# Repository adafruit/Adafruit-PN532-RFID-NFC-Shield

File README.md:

## Adafruit PN532 RFID/NFC Shield for Arduino
<a href="http://www.adafruit.com/products/789"><br/>
Click here to purchase one from the Adafruit shop</a>

We've taken our popular Adafruit PN532 breakout board and turned it into a shield - the perfect tool for any 13.56MHz RFID or NFC application. The Adafruit NFC shield uses the PN532 chip-set (the most popular NFC chip on the market) and is what is embedded in pretty much every phone or device that does NFC. It can pretty much do it all, such as read and write to tags and cards, communicate with phones (say for payment processing), and 'act' like a NFC tag. If you want to do any sort of embedded NFC work, this is the chip you'll want to use! 

These are the Eagle CAD files for the Adafruit PN532 RFID/NFC Shield for Arduino:
- http://www.adafruit.com/products/789

### License

Adafruit invests time and resources providing this open source design, please support Adafruit and open-source hardware by purchasing products from [Adafruit](https://www.adafruit.com)!

All text above must be included in any redistribution

Designed by Limor Fried/Ladyada and Kevin Townsend for Adafruit Industries.
Creative Commons Attribution/Share-Alike, all text above must be included in any redistribution. 
See license.txt for additional information.

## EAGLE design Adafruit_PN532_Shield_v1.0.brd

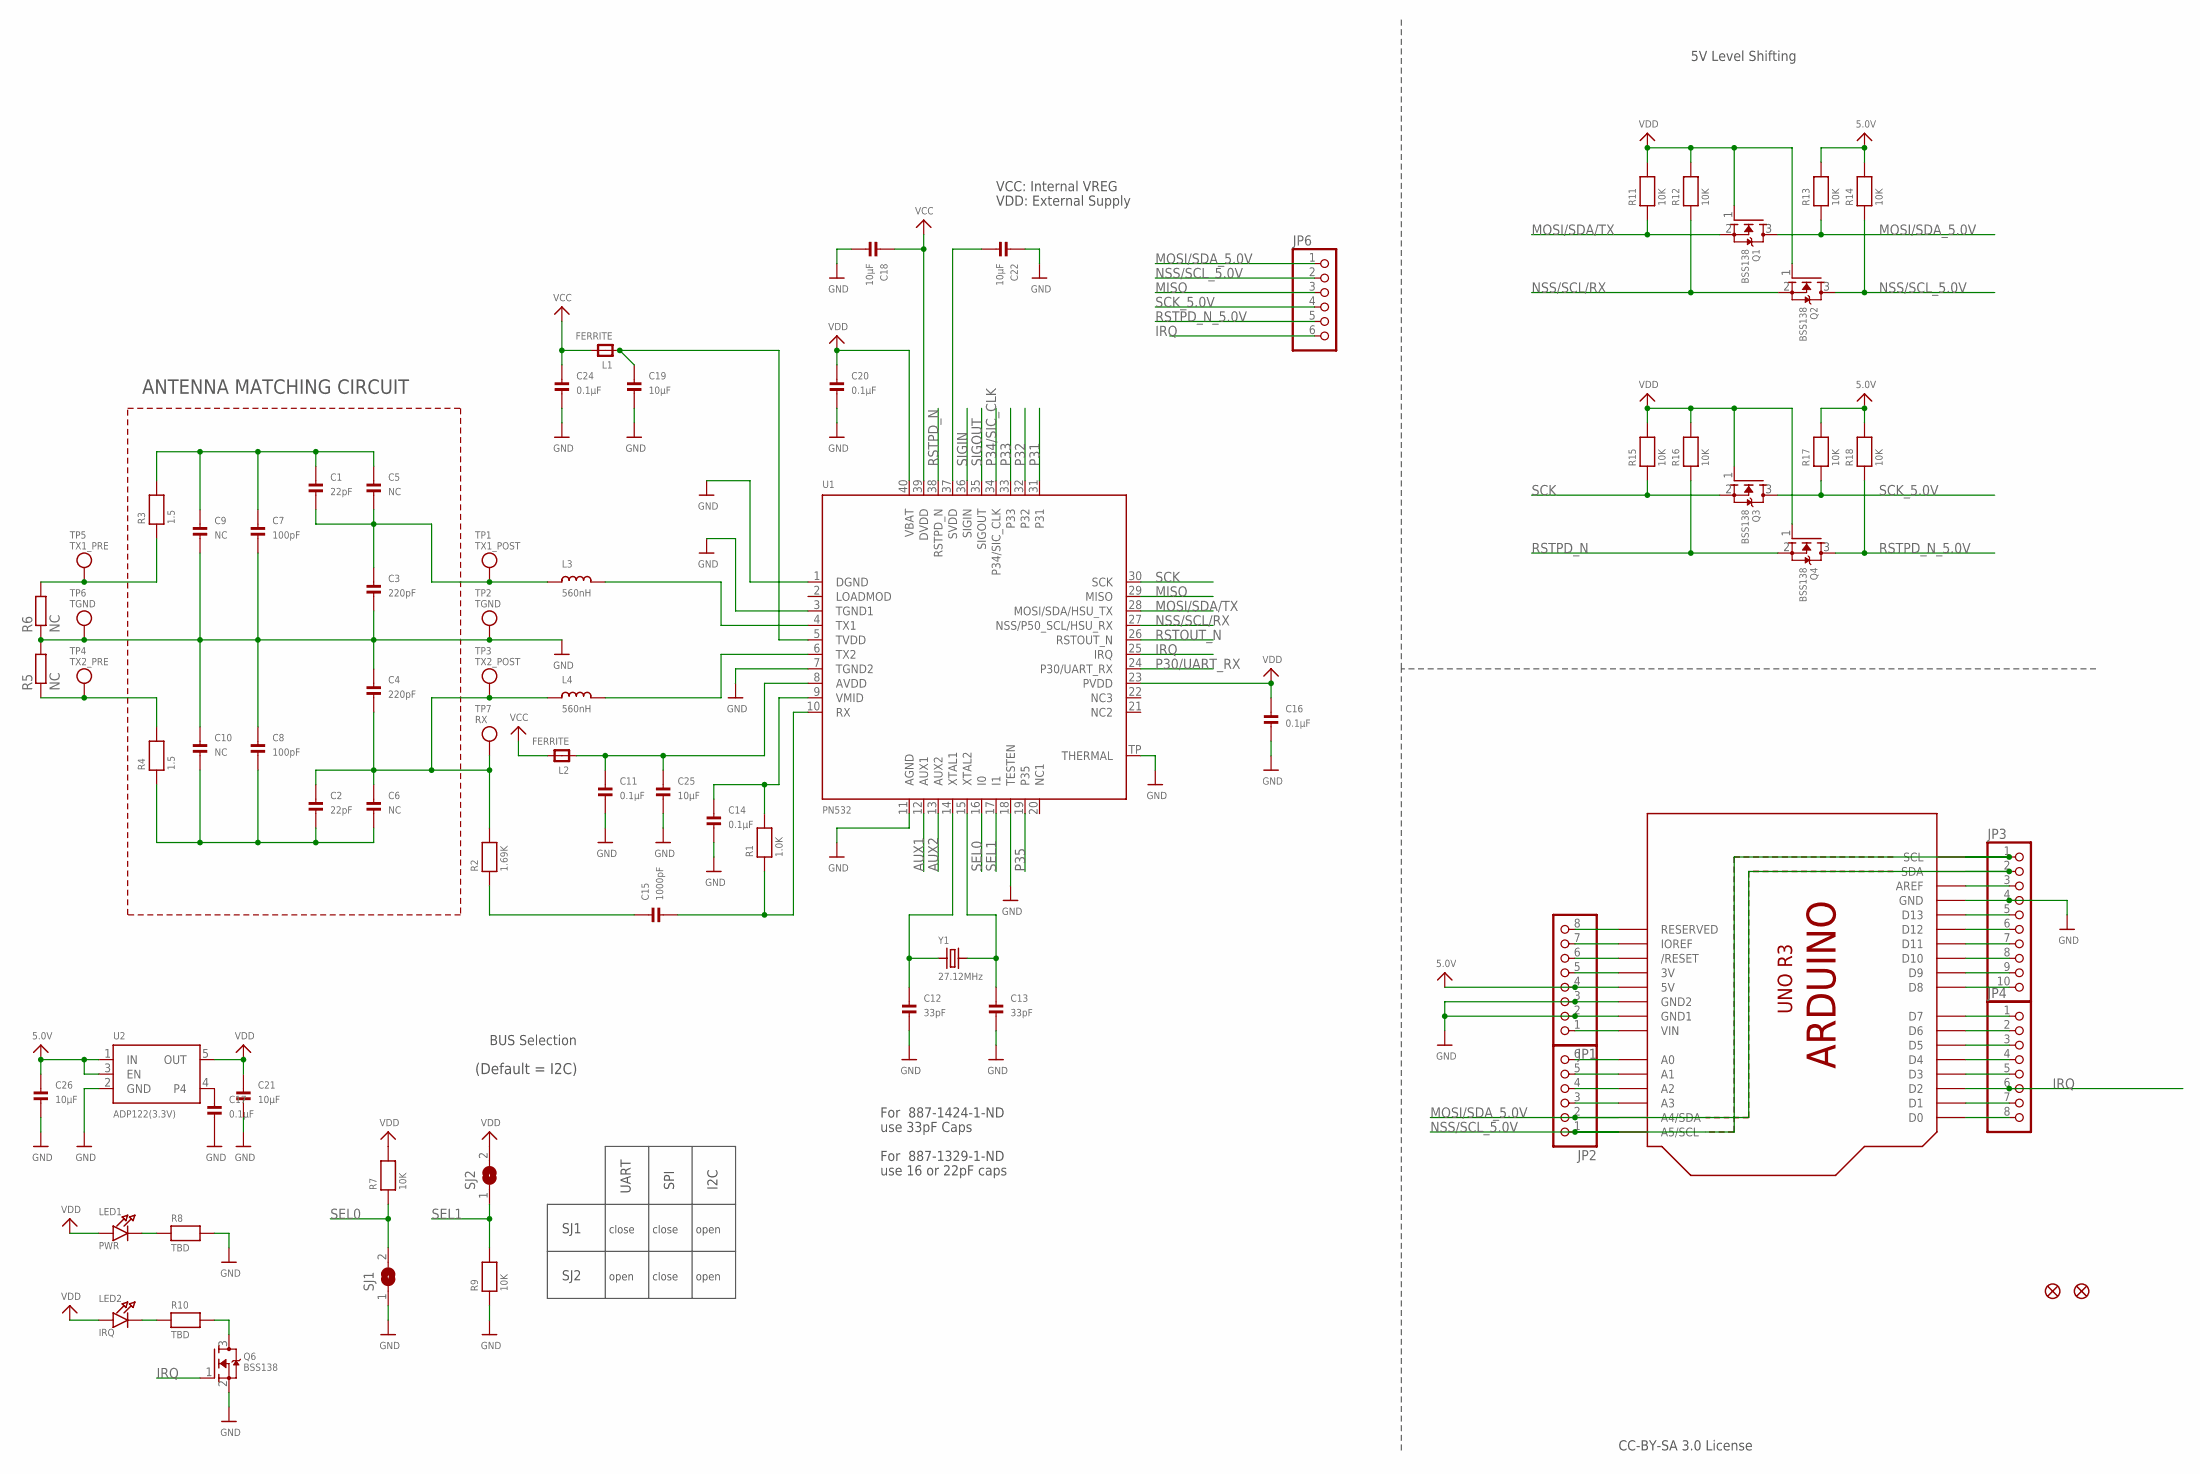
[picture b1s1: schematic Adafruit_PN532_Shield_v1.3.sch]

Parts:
C1, C2: 22pF; 0805
C3, C4: 220pF; 0805
C5, C6, C9, C10: NC; 0805
C7, C8: 100pF; 0805
C11, C14, C16, C17, C20, C24: 0.1µF; 0805
C12, C13: 33pF; 0805
C15: 1000pF; 0805
C18, C19, C21, C22, C25, C26: 10µF; 0805
FID1, FID2: FIDUCIAL1X2.5; FIDUCIAL-1X2.5
JP1, JP4: HEADER-1X870MIL; 1X08_ROUND_70
JP2: HEADER-1X670MIL; 1X06_ROUND_70
JP3: HEADER-1X1070MIL; 1X10_ROUND70
JP6: PINHD-1X6B; 1X06-BIG
L1, L2: FERRITE; 0805
L3, L4: 560nH; 0805
LED1: PWR; CHIPLED_0805
LED2: IRQ; CHIPLED_0805
Q1, Q2, Q3, Q4, Q6: BSS138; SOT23-WIDE
R1: 1.0K; 0805
R2: 1.69K; 0805
R3, R4: 1.5; 0805
R5, R6: NC; R0201
R7, R9, R11, R12, R13, R14, R15, R16, R17, R18: 10K; 0805
R8, R10: TBD; 0805
SJ1, SJ2: SOLDERJUMPERREFLOW_NOPASTE; SOLDERJUMPER_REFLOW_NOPASTE
TP1: TX1_POST; TESTPOINT_PAD_2MM
TP2, TP6: TGND; TESTPOINT_PAD_2MM
TP3: TX2_POST; TESTPOINT_PAD_2MM
TP4: TX2_PRE; TESTPOINT_PAD_2MM
TP5: TX1_PRE; TESTPOINT_PAD_2MM
TP7: RX; TESTPOINT_PAD_2MM
U1: PN532; HVQFN40-6X6
U2: ADP122(3.3V); SOT23-5
U3: ARDUINOR3NODIM; ARDUINOR3-NODIM
Y1: 27.12MHz; CRYSTAL_3.2X2.5

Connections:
5.0V: C26.1, JP1.4, R13.2, R14.2, R17.2, R18.2, U2.1 (IN), U2.3 (EN), U3.5V
AUX1: U1.12 (AUX1)
AUX2: U1.13 (AUX2)
GND: C3.2, C4.1, C7.2, C8.1, C9.2, C10.1, C11.2, C12.2, C13.2, C14.2, C16.2, C17.2, C18.2, C19.2, C20.2, C21.2, C22.1, C24.2, C25.2, C26.2, JP1.2, JP1.3, JP3.4, Q6.2 (S), R5.2, R6.1, R8.2, R9.1, SJ1.1, TP2.P$1, TP6.P$1, U1.1 (DGND), U1.3 (TGND1), U1.7 (TGND2), U1.11 (AGND), U1.18 (TESTEN), U1.TP (THERMAL), U2.2 (GND), U3.GND, U3.GND1, U3.GND2
IRQ: JP4.6, JP6.6, Q6.1 (G), U1.25 (IRQ), U3.D2
MISO: JP6.3, U1.29 (MISO)
MOSI/SDA/TX: Q1.2 (S), R11.1, U1.28 (MOSI/SDA/HSU_TX)
MOSI/SDA_5.0V: JP2.2, JP3.2, JP6.1, Q1.3 (D), R13.1, U3.A4 (A4/SDA), U3.SDA
unnamed: L3.2, U1.4 (TX1)
unnamed: L4.2, U1.6 (TX2)
unnamed: C1.2, C3.1, C5.2, L3.1, TP1.P$1
unnamed: R3.1, R6.2, TP5.P$1
unnamed: R4.2, R5.1, TP4.P$1
unnamed: LED1.C, R8.1
unnamed: C12.1, U1.14 (XTAL1), Y1.1
unnamed: C13.1, U1.15 (XTAL2), Y1.2
unnamed: C15.1, R2.1
unnamed: C14.1, R1.2, U1.9 (VMID)
unnamed: C15.2, R1.1, U1.10 (RX)
unnamed: C2.1, C4.2, C6.1, L4.1, R2.2, TP3.P$1, TP7.P$1
unnamed: C11.1, C25.1, L2.1, U1.8 (AVDD)
unnamed: C19.1, L1.1, U1.5 (TVDD)
unnamed: JP1.1, U3.VIN
unnamed: JP1.5, U3.3V
unnamed: JP1.6, U3.RESET (/RESET)
unnamed: JP1.7, U3.IOREF
unnamed: JP1.8, U3.RESERVED
unnamed: JP2.3, U3.A3
unnamed: JP2.4, U3.A2
unnamed: JP2.5, U3.A1
unnamed: JP2.6, U3.A0
unnamed: JP3.3, U3.AREF
unnamed: JP3.5, U3.D13
unnamed: JP3.6, U3.D12
unnamed: JP3.7, U3.D11
unnamed: JP3.8, U3.D10
unnamed: JP3.9, U3.D9
unnamed: JP3.10, U3.D8
unnamed: JP4.1, U3.D7
unnamed: JP4.2, U3.D6
unnamed: JP4.3, U3.D5
unnamed: JP4.4, U3.D4
unnamed: JP4.5, U3.D3
unnamed: LED2.C, R10.1
unnamed: JP4.7, U3.D1
unnamed: JP4.8, U3.D0
unnamed: Q6.3 (D), R10.2
unnamed: C17.1, U2.4
NSS/SCL/RX: Q2.2 (S), R12.1, U1.27 (NSS/P50_SCL/HSU_RX)
NSS/SCL_5.0V: JP2.1, JP3.1, JP6.2, Q2.3 (D), R14.1, U3.A5 (A5/SCL), U3.SCL
P30/UART_RX: U1.24 (P30/UART_RX)
P31: U1.31
P32: U1.32
P33: U1.33
P34/SIC_CLK: U1.34 (P34/SIC_CLK)
P35: U1.19 (P35)
RSTOUT_N: U1.26 (RSTOUT_N)
RSTPD_N: Q4.2 (S), R16.1, U1.38 (RSTPD_N)
RSTPD_N_5.0V: JP6.5, Q4.3 (D), R18.1
SCK: Q3.2 (S), R15.1, U1.30 (SCK)
SCK_5.0V: JP6.4, Q3.3 (D), R17.1
SEL0: R7.1, SJ1.2, U1.16 (I0)
SEL1: R9.2, SJ2.1, U1.17 (I1)
SIGIN: U1.36 (SIGIN)
SIGOUT: U1.35 (SIGOUT)
TX1_ANTENNA: C1.1, C5.1, C7.1, C9.1, R3.2
TX2_ANTENNA: C2.2, C6.2, C8.2, C10.2, R4.1

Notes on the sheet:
ANTENNA MATCHING CIRCUIT
SJ1
SJ2
UART
SPI
I2C
close
open
CC-BY-SA 3.0 License
For 887-1329-1-ND
use 16 or 22pF caps
For 887-1424-1-ND
use 33pF Caps
BUS Selection
(Default = I2C)
5V Level Shifting
VCC: Internal VREG
VDD: External Supply

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
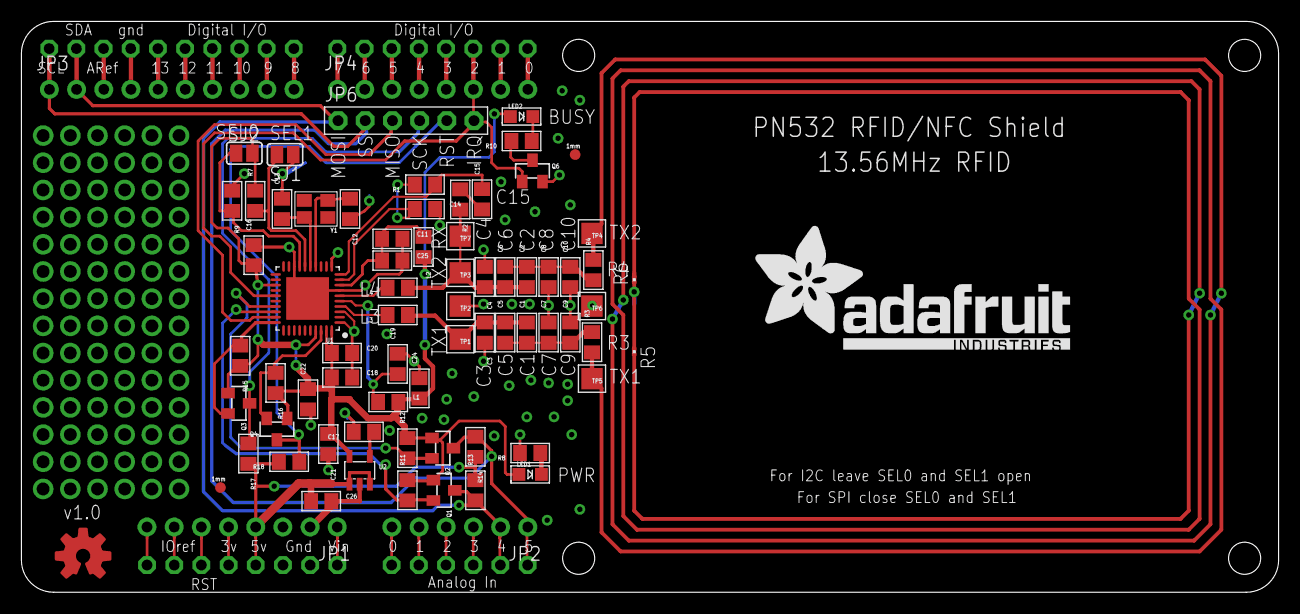
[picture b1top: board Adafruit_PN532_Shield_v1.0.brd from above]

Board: 2 copper layers, 117.5 x 53.3 mm, 76 parts (0 on the bottom side), 57 nets.

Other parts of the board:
U$3: ADAFRUIT_TEXT_30MM
U$50: OSHWLOGO_TOP_0.2

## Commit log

2012-05-31 init
2012-05-31 added kevin!
2016-03-16 added dimensions to board. generated pdfs
2016-03-22 latest version
